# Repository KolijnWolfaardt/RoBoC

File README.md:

# RoBoC
The RoBoC is a robotics controller board designed for the Robotics club of Stellenbosch. It features a dsPIC33 microcontroller, a motor river and plenty of IO pins. This was designed to be cheaper than off the shelf development boards with the necessary extras.

Please see the full documentation at [http://kolijnwolfaardt.github.io/RoBoC/](http://kolijnwolfaardt.github.io/RoBoC/)

# About the PCB Design
The PCB is designed in [Kicad](www.kicad-pcb.org/). All the project files can be found in *./PCB Design*, and the extra component footprints created are in *./PCB Design/lib*. Some of these components are adapted from the libraries supplied with KiCad. 

The board was originally designed as a 4 layer board, with power and some signals on the inner copper layers. This proved to be too expensive, so the board was redesigned as a 2-layer board.

# Bootloader
## ds30 Bootloader
The ds30 Bootloader code supplied here is a modified version of the [ds30 Loader](http://picbootloader.com/). The following changes were made:

 - The initialization includes configuring the oscillator and PLL
 - The UART initialization was simplified.
 - An LED on the board is turne on and off to indicate when the bootloader is waiting for commands.
 - The memory footprint of the bootloader was reduces by commenting out some of the original (unused) code.

### Compiling the Bootloader
To compile the bootloader the MPLAB IDE v8.92 and the ASM30 compiler were used, on a pc running Windows. The resulting hex file can be written to the board using a PicKit2 or PicKit3.

### Using the Bootloader
To use the bootloader, use the program supplied on the ds30 Loader website.

# Technical Details
 - The Microcontroller is a [dsPic33FJ32GS606](http://www.microchip.com/wwwproducts/Devices.aspx?dDocName=en546851)
 - USB to UART IC is a [MCP2200](http://www.microchip.com/wwwproducts/devices.aspx?dDocName=en546923)
 - The Motor driver is a ON Semiconductor [LV8405V](http://www.onsemi.com/PowerSolutions/product.do?id=LV8405V)
 - The PCB is a 2-layer 5cm by 10cm board

# License
 - The Hardware is licensed under the [CERN OSH License ](http://www.ohwr.org/attachments/2388/cern_ohl_v_1_2.txt)
 - The ds30 Bootloader is licensed under the [GNU GPLv2 Licens](http://www.gnu.org/licenses/old-licenses/gpl-2.0.en.html)
 - Software written for the board is licensed under the [CC Attribution-NonCommerical License ](https://creativecommons.org/licenses/by-nc/2.0/legalcode)

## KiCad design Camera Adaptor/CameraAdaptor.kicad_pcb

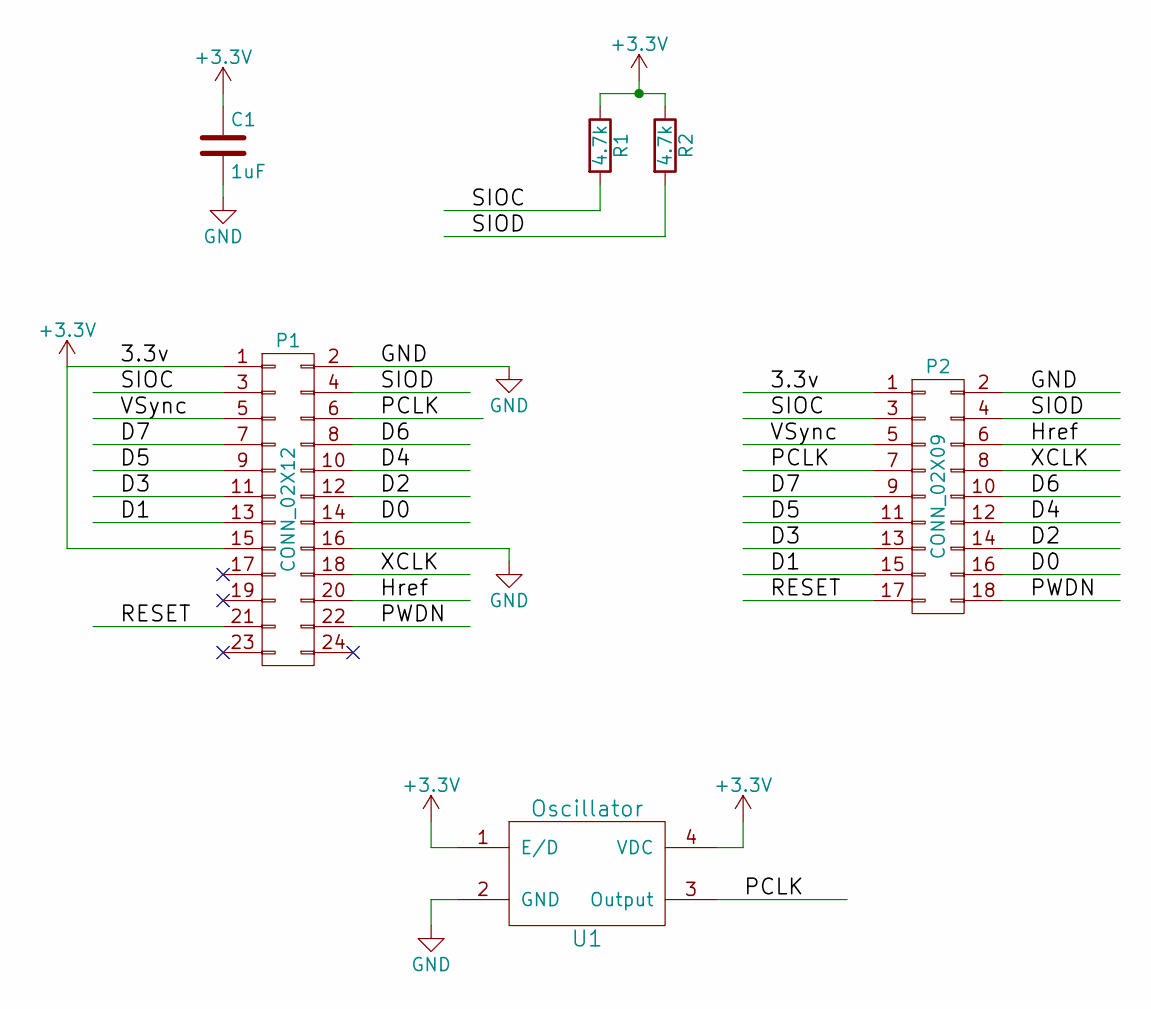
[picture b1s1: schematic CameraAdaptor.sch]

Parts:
C1: 1uF; C_1206_HandSoldering
P1: CONN_02X12; Pin_Header_Straight_2x12
P2: CONN_02X09; Pin_Header_Straight_2x09
R1, R2: 4.7k; R_1206_HandSoldering
U1: Oscillator; oscillator

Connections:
+3V3: C1.1, P1.1, P1.15, P2.1, R1.1, R2.1, U1.1 (E/D), U1.4 (VDC)
/D0: P1.14, P2.16
/D1: P1.13, P2.15
/D2: P1.12, P2.14
/D3: P1.11, P2.13
/D4: P1.10, P2.12
/D5: P1.9, P2.11
/D6: P1.8, P2.10
/D7: P1.7, P2.9
/Href: P1.20, P2.6
/PCLK: P1.6, P2.7, U1.3 (Output)
/PWDN: P1.22, P2.18
/RESET: P1.21, P2.17
/SIOC: P1.3, P2.3, R1.2
/SIOD: P1.4, P2.4, R2.2
/VSync: P1.5, P2.5
/XCLK: P1.18, P2.8
GND: C1.2, P1.2, P1.16, P2.2, U1.2 (GND)

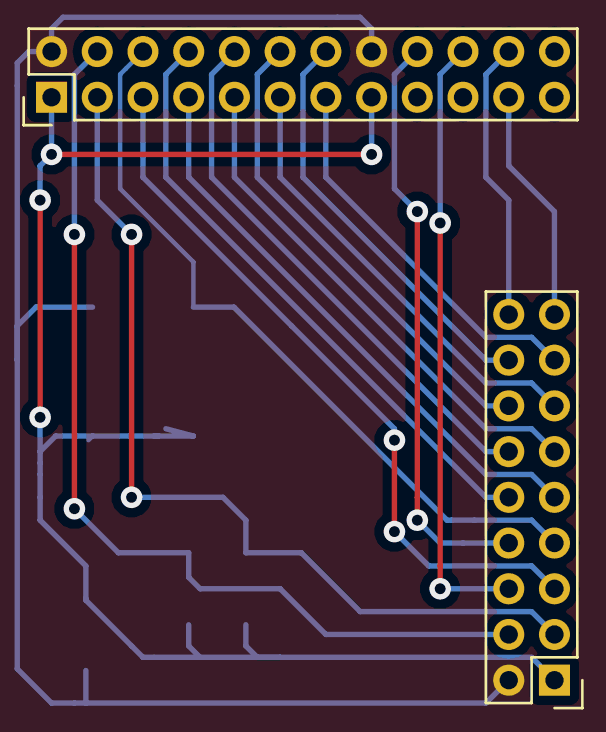
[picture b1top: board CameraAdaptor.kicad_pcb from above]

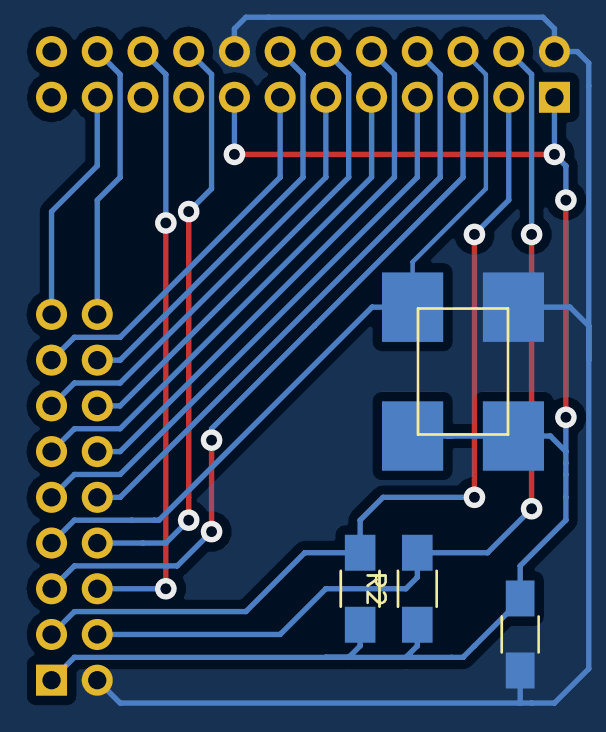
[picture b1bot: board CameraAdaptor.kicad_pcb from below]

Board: 2 copper layers, 6 parts (4 on the bottom side), 18 nets.

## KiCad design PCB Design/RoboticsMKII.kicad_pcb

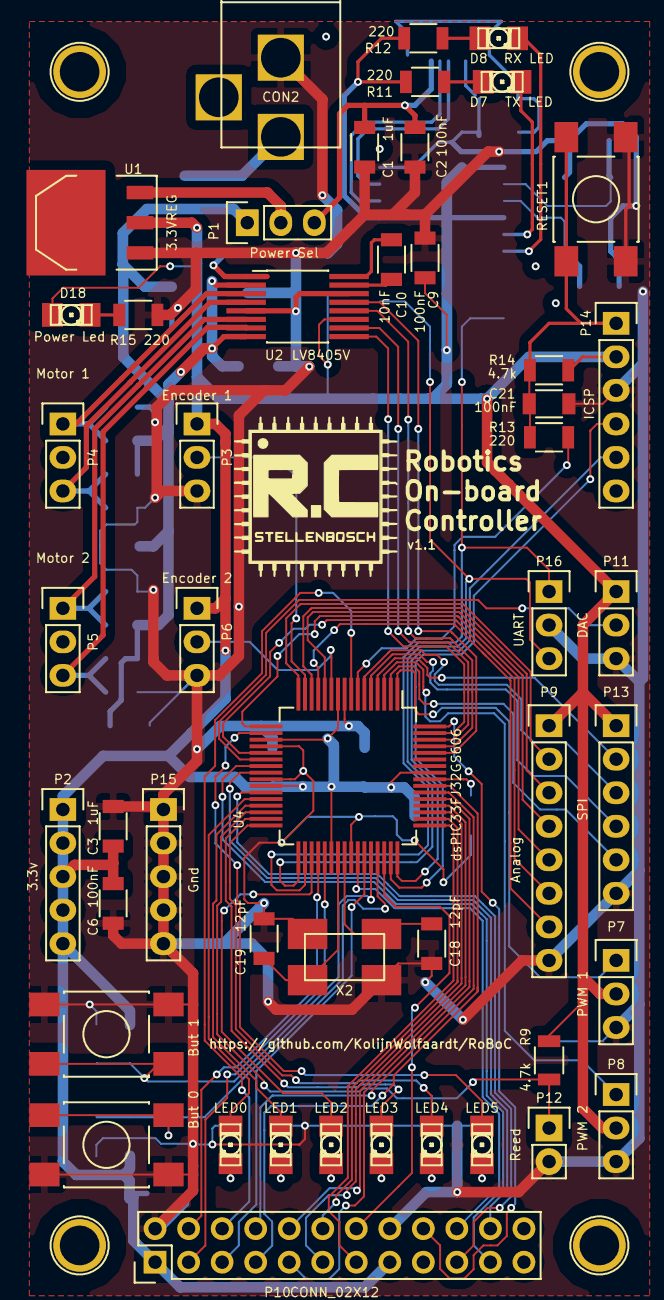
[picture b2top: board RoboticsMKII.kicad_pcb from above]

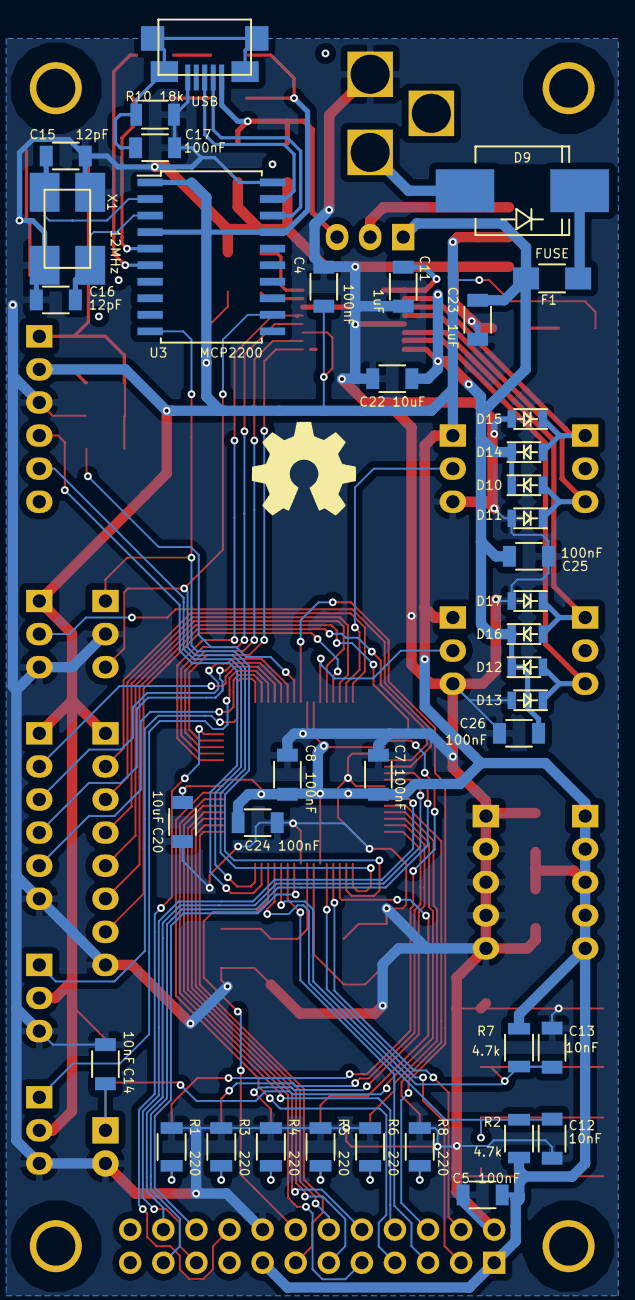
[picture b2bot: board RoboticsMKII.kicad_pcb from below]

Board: 2 copper layers, 91 parts (39 on the bottom side), 84 nets.

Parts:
C1, C3, C4, C23: 1uF; C_1206
C2, C5, C6, C7, C8, C9, C11, C17, C21, C24, C25, C26: 100nF; C_1206
C10, C12, C13, C14: 10nF; C_1206
C15, C16, C18, C19: 12pF; C_1206
C20, C22: 10uF; C_1206
CON1: USB; USB_Micro
CON2: BARREL_JACK
D1: LED5; LED-1206
D2: LED4; LED-1206
D3: LED3; LED-1206
D4: LED2; LED-1206
D5: LED1; LED-1206
D6: LED0; LED-1206
D7: TX LED; LED-1206
D8: RX LED; LED-1206
D9: D; Diode-SMC_Handsoldering
D10, D11, D12, D13, D14, D15, D16, D17: D; SOD-323
D18: Power Led; LED-1206
F1: FUSE; R_1206_HandSoldering
P1: Power Sel; Pin_Header_Straight_1x03
P2: 3.3v; Pin_Header_Straight_1x05
P3: Encoder 1; Pin_Header_Straight_1x03
P4: Motor 1; Pin_Header_Straight_1x03
P5: Motor 2; Pin_Header_Straight_1x03
P6: Encoder 2; Pin_Header_Straight_1x03
P7: PWM 1; Pin_Header_Straight_1x03
P8: PWM 2; Pin_Header_Straight_1x03
P9: Analog; Pin_Header_Straight_1x08
P10: CONN_02X12; Pin_Header_Straight_2x12
P11: DAC; Pin_Header_Straight_1x03
P12: Reed; Pin_Header_Straight_1x02
P13: SPI; Pin_Header_Straight_1x06
P14: ICSP; Pin_Header_Straight_1x06
P15: Gnd; Pin_Header_Straight_1x05
P16: UART; Pin_Header_Straight_1x03
P96, P97, P98, P99: CONN_01X01; MountingHole3mm
R1, R3, R4, R5, R6, R8, R11, R12, R13, R15: 220; R_1206
R2, R7, R9, R14: 4.7k; R_1206
R10: 18k; R_1206
RESET1: DPST; SW_SPST_bigpads
SW0: But 0; SW_SPST_bigpads
SW1: But 1; SW_SPST_bigpads
U1: 3.3VREG; SOT-223
U2: LV8405V; SSOP-16_4.4x5.2mm_Pitch0.65mm_Handsoldering
U3: MCP2200; SOIC-20_7.5x12.8mm_Pitch1.27mm
U4: dsPIC33FJ32GS606; TQFP-64_10x10mm_Pitch0.5mm_handsoldering
X1: 12MHz; Crystal 6x 3.5 x 1.1mm
X2: 10MHz; Crystal 6x 3.5 x 1.1mm

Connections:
/gpio/AN0: P9.2, U4.16
/gpio/AN1: P9.3, U4.14
/gpio/AN2: P9.4, U4.12
/gpio/AN3: P9.5, U4.17
/gpio/AN4: P9.6, U4.21
/gpio/AN5: P9.7, U4.13
/gpio/BUT_0: C12.2, R2.2, SW0.1, U4.45
/gpio/BUT_1: C13.2, R7.2, SW1.1, U4.44
/gpio/DACOUT: P11.2, U4.22
/gpio/DATA_0: P10.14, U4.46
/gpio/DATA_1: P10.13, U4.49
/gpio/DATA_2: P10.12, U4.50
/gpio/DATA_3: P10.11, U4.51
/gpio/DATA_4: P10.10, U4.52
/gpio/DATA_5: P10.9, U4.53
/gpio/DATA_6: P10.8, U4.54
/gpio/DATA_7: P10.7, U4.55
/gpio/Href: P10.6, U4.8
/gpio/LED0: D6.1, U4.28
/gpio/LED1: D5.1, U4.29
/gpio/LED2: D4.1, U4.35
/gpio/LED3: D3.1, U4.31
/gpio/LED4: D2.1, U4.32
/gpio/LED5: D1.1, U4.18
/gpio/RCK: P10.18, U4.64
/gpio/Reed: C14.2, P12.1, R9.2, U4.30
/gpio/SIO_C: P10.3, U4.37
/gpio/SIO_D: P10.4, U4.36
/gpio/SPI_CLK: P13.2, U4.4
/gpio/SPI_MISO: P13.4, U4.5
/gpio/SPI_MOSI: P13.3, U4.6
/gpio/SPI_SS: P13.5, U4.2
/gpio/vSync: P10.5, U4.43
/gpio/~OE: P10.20, U4.42
/gpio/~RRST: P10.22, U4.24
/gpio/~WR: P10.19, U4.27
/gpio/~WRST: P10.21, U4.23
/mcu/MCLR: R13.2, U4.7
/mcu/MCLR_in: C21.1, P14.1, R13.1, R14.1, RESET1.1
/mcu/MOT1_D1: U2.13, U4.60
/mcu/MOT1_D2: U2.12, U4.61
/mcu/MOT1_ENC: P3.2, U4.15
/mcu/MOT2_D1: U2.10, U4.62
/mcu/MOT2_D2: U2.9, U4.63
/mcu/MOT2_ENC: P6.2, U4.11
/mcu/OSC1: C18.2, U4.40, X2.1
/mcu/OSC2: C19.2, U4.39, X2.2
/mcu/PGC: P14.5, U4.48
/mcu/PGD: P14.4, U4.47
/mcu/Vcap: C20.2, U4.56
/motors/C1H: C10.1, U2.16
/motors/C1L: C10.2, U2.15
/motors/MOT1_1: D14.1, D15.2, P4.1, U2.3
/motors/MOT1_2: D10.1, D11.2, P4.3, U2.4
/motors/MOT2_1: D16.1, D17.2, P5.1, U2.6
/motors/MOT2_2: D12.1, D13.2, P5.3, U2.7
/motors/PWM1: P7.1, U4.1
/motors/PWM2: P8.1, U4.3
/motors/VG: C11.1, U2.1
/motors/V_Bat: C22.1, C23.1, C25.1, C26.1, D10.2, D12.2, D14.2, D16.2, F1.2, P1.1, U2.2, U2.8
/power/V_USB: C1.1, C2.1, CON1.1, P1.3
/usb/MCU_RX: P16.1, U3.10, U4.34
/usb/MCU_TX: P16.3, U3.12, U4.33
/usb/RX_LED: D8.2, U3.6
/usb/TX_LED: D7.2, U3.5
/usb/USB_D+: CON1.3, U3.19
/usb/USB_D-: CON1.2, U3.18
/usb/USB_OSC1: C15.1, U3.2, X1.1
/usb/USB_OSC2: C16.1, U3.3, X1.2
GND: C1.2, C2.2, C3.2, C4.2, C5.2, C6.2, C7.2, C8.2, C9.2, C11.2, C12.1, C13.1, C14.1, C15.2, C16.2, C17.2, C18.1, C19.1, C20.1, C21.2, C22.2, C23.2, C24.2, C25.2, C26.2, CON1.5, CON2.2, D11.1, D13.1, D15.1, D17.1, P3.3, P6.3, P7.3, P8.3, P9.8, P10.2, P10.16, P11.3, P12.2, P13.6, P14.3, P15.1, P15.2, P15.3, P15.4, P15.5, P16.2, R1.2, R3.2, R4.2, R5.2, R6.2, R8.2, R10.2, R15.2, RESET1.2, SW0.2, SW1.2, U1.1, U2.5, U2.14, U3.20, U4.9, U4.20, U4.25, U4.41, X1.3, X2.3
unnamed: C17.1, CON1.6, CON1.7, CON1.8, CON1.9, R10.1
unnamed: CON2.1, D9.1
unnamed: D1.2, R1.1
unnamed: D2.2, R3.1
unnamed: D3.2, R4.1
unnamed: D4.2, R5.1
unnamed: D5.2, R6.1
unnamed: D6.2, R8.1
unnamed: D7.1, R11.2
unnamed: D8.1, R12.2
unnamed: D9.2, F1.1
unnamed: D18.2, R15.1
unnamed: P1.2, U1.3
V3.3: C3.1, C4.1, C5.1, C6.1, C7.1, C8.1, C9.1, C24.1, D18.1, P2.1, P2.2, P2.3, P2.4, P2.5, P3.1, P6.1, P7.2, P8.2, P9.1, P10.1, P10.15, P11.1, P13.1, P14.2, R2.1, R7.1, R9.1, R11.1, R12.1, R14.2, U1.2, U2.11, U3.1, U3.4, U3.17, U4.10, U4.19, U4.26, U4.38, U4.57

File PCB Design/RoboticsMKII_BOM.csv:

C1, 1uF, Capacitors_SMD:C_1206,  
C2, 100nF, Capacitors_SMD:C_1206,  
C3, 1uF, Capacitors_SMD:C_1206,  
C4, 1uF, Capacitors_SMD:C_1206,  
C5, 100nF, Capacitors_SMD:C_1206,  
C6, 100nF, Capacitors_SMD:C_1206,  
C7, 100nF, Capacitors_SMD:C_1206,  
C8, 100nF, Capacitors_SMD:C_1206,  
C9, 100nF, Capacitors_SMD:C_1206,  
C10, 10nF, Capacitors_SMD:C_1206,  
C11, 100nF, Capacitors_SMD:C_1206, 
C12, 10nF, Capacitors_SMD:C_1206,  
C13, 10nF, Capacitors_SMD:C_1206,  
C14, 10nF, Capacitors_SMD:C_1206,  
C15, 22pF, Capacitors_SMD:C_1206,  
C16, 22pF, Capacitors_SMD:C_1206, 
C17, 100nF, Capacitors_SMD:C_1206, 
C18, 22pF, Capacitors_SMD:C_1206,  
C19, 22pF, Capacitors_SMD:C_1206,  
C20, 10uF, Capacitors_SMD:C_1206,  
C21, 100nF, Capacitors_SMD:C_1206,   
C22, 10uF, Capacitors_SMD:C_1206,  
C23, 1uF, Capacitors_SMD:C_1206,  

R1, 220, Resistors_SMD:R_1206,  
R2, 4.7k, Resistors_SMD:R_1206, 
R3, 220, Resistors_SMD:R_1206,  
R4, 220, Resistors_SMD:R_1206,  
R5, 220, Resistors_SMD:R_1206,  
R6, 220, Resistors_SMD:R_1206,  
R7, 4.7k, Resistors_SMD:R_1206, 
R8, 220, Resistors_SMD:R_1206,  
R9, 4.7k, Resistors_SMD:R_1206,  
R11, 220, Resistors_SMD:R_1206,  
R12, 220, Resistors_SMD:R_1206, 
R10, 18k, Resistors_SMD:R_1206, 
R13, 220, Resistors_SMD:R_1206,  
R14, 4.7k, Resistors_SMD:R_1206,  

F1, FUSE, ,  
 
D1, LED, LEDs:LED-1206, 
D2, LED, LEDs:LED-1206,  
D3, LED, LEDs:LED-1206,  
D4, LED, LEDs:LED-1206,  
D5, LED, LEDs:LED-1206,  
D6, LED, LEDs:LED-1206,  
D7, LED, LEDs:LED-1206,  
D8, LED, LEDs:LED-1206,  
D9, D, Diode,  

RESET1, DPST, Buttons_Switches_SMD:SW_SPST_PTS645,  
SW0, DPST, Buttons_Switches_SMD:SW_SPST_PTS645,  
SW1, DPST, Buttons_Switches_SMD:SW_SPST_PTS645,  

CON1, USB-MICRO-B, USB,  
 
U1, 3.3VREG, ,  
U2, LV8405V, ,  
U3, MCP2200, ,  
U4, dsPIC33FJ32GS606, TQFP,  

X1, 12MHz, ,  
X2, 10MHz, ,  
 
P1, CONN_01X03, Pin_Headers:Pin_Header_Straight_1x03,  
P2, CONN_01X02, ,  
P3, CONN_01X03, Pin_Headers:Pin_Header_Straight_1x03,  
P4, CONN_01X03, Pin_Headers:Pin_Header_Straight_1x03,  
P5, CONN_01X03, Pin_Headers:Pin_Header_Straight_1x03,  
P6, CONN_01X03, Pin_Headers:Pin_Header_Straight_1x03,  
P7, CONN_01X03, Pin_Headers:Pin_Header_Straight_1x03,  
P8, CONN_01X03, Pin_Headers:Pin_Header_Straight_1x03,  
P9, CONN_01X08, Pin_Headers:Pin_Header_Straight_1x08,  
P10, CONN_02X11, Pin_Headers:Pin_Header_Straight_2x11,  
P11, CONN_01X03, Pin_Headers:Pin_Header_Straight_1x03, 
P12, CONN_01X02, Pin_Headers:Pin_Header_Straight_1x02, 
P13, CONN_01X06, Pin_Headers:Pin_Header_Straight_1x06,  
P14, CONN_01X06, Pin_Headers:Pin_Header_Straight_1x06,

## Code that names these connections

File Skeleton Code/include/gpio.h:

/* 
 * File:   gpio.h
 * Author: Kolijn
 *
 * Created on May 31, 2015, 7:58 AM
 */

#ifndef GPIO_H
#define	GPIO_H


#define LED0 LATBbits.LATB13
#define LED1 LATBbits.LATB14
#define LED2 LATFbits.LATF6
#define LED3 LATFbits.LATF4
#define LED4 LATFbits.LATF5
#define LED5 LATBbits.LATB7

#define BUT0 PORTDbits.RD11
#define BUT1 PORTDbits.RD10

#define SERVO_1 PORTEbits.RE5
#define SERVO_2 PORTEbits.RE7



#define SIO_C       PORTGbits.RG2
#define SIO_D       PORTGbits.RG3
//VSyn is an input
#define VSYNC       PORTDbits.RD9
//HRef is an input
///Href and PCLK (Previously OE) are swapped
#define HREF        PORTDbits.RD8
//PCLK is named OE in the spreadsheet
//PCLK (previously OE) and Href are swapped
#define PCLK        PORTGbits.RG9
//XCLK is named RCK in the spreadsheet 
#define XCLK        LATEbits.LATE4 
#define CAM_DATA    PORTD
#define RESET       LATBbits.LATB10
#define PWDN        LATBbits.LATB11

#define MOT1_D1 PORTEbits.RE0
#define MOT1_D2 PORTEbits.RE1
#define MOT1_ENC PORTBbits.RB1
#define MOT2_D1 PORTEbits.RE2
#define MOT2_D2 PORTEbits.RE3
#define MOT2_ENC PORTBbits.RB5

#define SPISS PORTEbits.RE6

void setup_gpio();
void led_write(int num);

#endif

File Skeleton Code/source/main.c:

#include <stdlib.h>
#include <xc.h>

#include "hardware_config.h"
#include "adc.h"
#include "camera.h"
#include "gpio.h"
#include "servo.h"
#include "timer.h"
#include "uart.h"





/* =========================================================
 *              Function Prototypes
 * ====================================================== */

/* =========================================================
 *              Global Variables
 * ====================================================== */
int but0_down = 0;
int but1_down = 0;
int led_number = 0;

/* =========================================================
 *              Interrupt Service Routines
 * ====================================================== */



/* =========================================================
 *              Main function
 * ====================================================== */
int main(int argc, char** argv)
{
    configure_oscillator();
    setup_gpio(); 
    setup_uart();
    setup_pwm();
    setup_adc();
    setup_timer_1();
    setup_camera(); 
    
    // Uncomment to enable the ADC
    //adc_enable();
    
    //THis is for camera debugging
    //Use the SPI_SS pin as an output
    TRISEbits.TRISE6 = 0; 
    //Use the SPI_miso pin as an ouput
    TRISGbits.TRISG7 = 0;
   
    while(1)
    {
        //Check for button 0
        if (but0_down == 0)
        {
            if (BUT0 == 0)
            {
                led_number++;
                led_write(led_number);
                
                but0_down = 1;
            }
        }
        else
        {
            if (BUT0 == 1)
            {
                but0_down = 0;
            }
        }
        
        //Check for button 1
        if (but1_down == 0)
        {
            if (BUT1 == 0)
            {
                led_number--;
                led_write(led_number);
                
                but1_down = 1;
            }
        }
        else
        {
            if (BUT1 == 1)
            {
                but1_down = 0;
            }
        }
        
        //Check the milliseconds
        if (millis()>10)
            LED0 = 0;
        else
            LED0 =1;

        
        if(rx_flag==1)
        {
            capture_camera();
            rx_flag=0;
        }
    }
    
}

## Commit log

2015-03-26 First Commit, most of the circuit layout.
    Ths biggest part of the circuit layout is completed. Minor fixes are still
    required, and some design changes.
2015-03-26 Changed power input to diode and fuse, fixed pinout
    The power input is now protected by a diode and fuse in series.
    The pinout of the PIC is fixed, pin 17 is now RB6 rather than RA6
2015-03-26 Added pdf plot
2015-03-28 Added initial footprint associations, caps and resistors.
    Kicad is giving weird errors for the libraries and BOM generator.
    The libraries have to be downloaded manually from github, and
    then added.
2015-03-30 Added diodes to motor driver
2015-03-30 Added crystal footprint
2015-03-31 Finished the footprint allocation, started on the PCB layout.-s
2015-04-02 Added UART, Gnd and 3.3v pins
2015-04-02 PCB is now 10cmx5cm, some components moved around for more space
2015-04-02 Connected 2nd floating ground to ground (updated pdf and .net to reflect this)
2015-04-02 Current ideas on pcb layout added
2015-04-05 Removed connection between data_4 and data_5
2015-04-05 Motor Diodes done, some of the power connections
2015-04-05 More power layout, improved feedback diodes. All fonts now the same
2015-04-05 Bus routing done. No idea what to do with the MCU oscillator.
2015-04-06 Removed bus, rotated mcu to fit crystal in
2015-04-06 Most of the Camera bus routed, analog bus routed as well. ICSP and SPI are next
2015-04-06 Most signals are done now, only power remains. This will definitely be a 4 layer board
2015-04-06 Done with the power layout.
2015-04-06 Added an additional cap for the MCU, added copper fill on all layers.
2015-04-06 Added OSHW logo on the back and front text. Filled copper and generated gerbers.
2015-04-15 Added caps next to motor feedback diodes
2015-04-19 Did some fixes, added better footprint for the flyback diodes:
    Re-routed camera bus so that there is more ground for the crystal.
    Added ground pour keepouts under the MCU.
    Changed the footprint for the motor flyback diodes.
    Changed the camera module to have 24 pins, 2 won't be connected
    Checked the footprints for dsPIC, MCP and LV8045
    Increased thermal pad for voltage regulator
2015-04-19 More Changes:
    Checked top and bottom silkscreen - almost no overlaps with pads or holes
    Added Robotic club logo to board, generated from png file.
    Modified on-board text.
2015-04-20 Moved all fabrication layer to silkscreen
    Moved tracks to look better with copper pour
    Fixed more silscreen-on-via errors
2015-04-20 Fixed some DRC issues, connected ground traces
    No more unccenected pads now
2015-04-20 Added keepout under some components
2015-04-21 Some small changes
2015-04-23 Increased pad sizes for easy soldering, final commit before ordering
2015-05-05 Some changes?
2015-05-05 Started 2 layer layout
2015-05-05 Many buslines done, camera bus almost there, LED bus almost done, analog bus almost. SPI and pwm needs attention
2015-05-05 More done. PWM and SPI need attention
2015-05-06 Finished 2-layer routing, now it needs to be checked
2015-05-06 2layers almost done. Silkscreen needs checking
2015-05-06 Top Silkscreen fixed. Almost done
2015-05-07 Changed all via sizes, changed layout, changed jack footprint to original
2015-05-08 Final version
2015-06-02 Merged 2Layer branch, added license info
2015-06-06 Added working ds30 Bootloader, updated Licenses and readme
2015-08-07 Added the camera adapter-s
2015-08-08 Added correct bootloader code, with hex output file
2015-08-09 First version of the pages
2015-08-11 Changed to jekyll engine for publishing
2015-08-11 Added transitions, correct css file and MediaQueries
2015-08-11 Did the basic layout, avaiting via size, track width specifications.
2015-08-14 Changed CamerAdaptor layout, changed track thickness
2015-08-17 Added more content, Fixed CSS when screen is resized
2015-08-19 Removed pdf outputs, added correct gerber files
    One of the gerber files doesn't register correct with
    the cnc machine: The hole should be positioned at 80,100
    but ends at 800,100
2015-08-19 Added Skeleton code
2015-08-20 Fixed bootloader, added link, fixed skeleton code
2015-08-20 Fixed link
2015-08-21 Fixed camera board
2015-08-23 Wrote a little bit about the camera
2015-08-24 Wrote about the skeleton code
2015-08-24 Bootloader again. Hopefully correct this time
2015-08-25 Added well-commented skeleton code, and scripts to get the image
